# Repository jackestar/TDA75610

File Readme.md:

# TDA75610 Development Board (Placa de desarrollo)

[Blog](https://jackestar.netlify.app/Blog/Kicad/TDA75610.html)
[Esquematico](https://drive.google.com/file/d/1zOZ_QLpb7rlT-NX607TR__lV9A5XwjoH/view?usp=sharing)

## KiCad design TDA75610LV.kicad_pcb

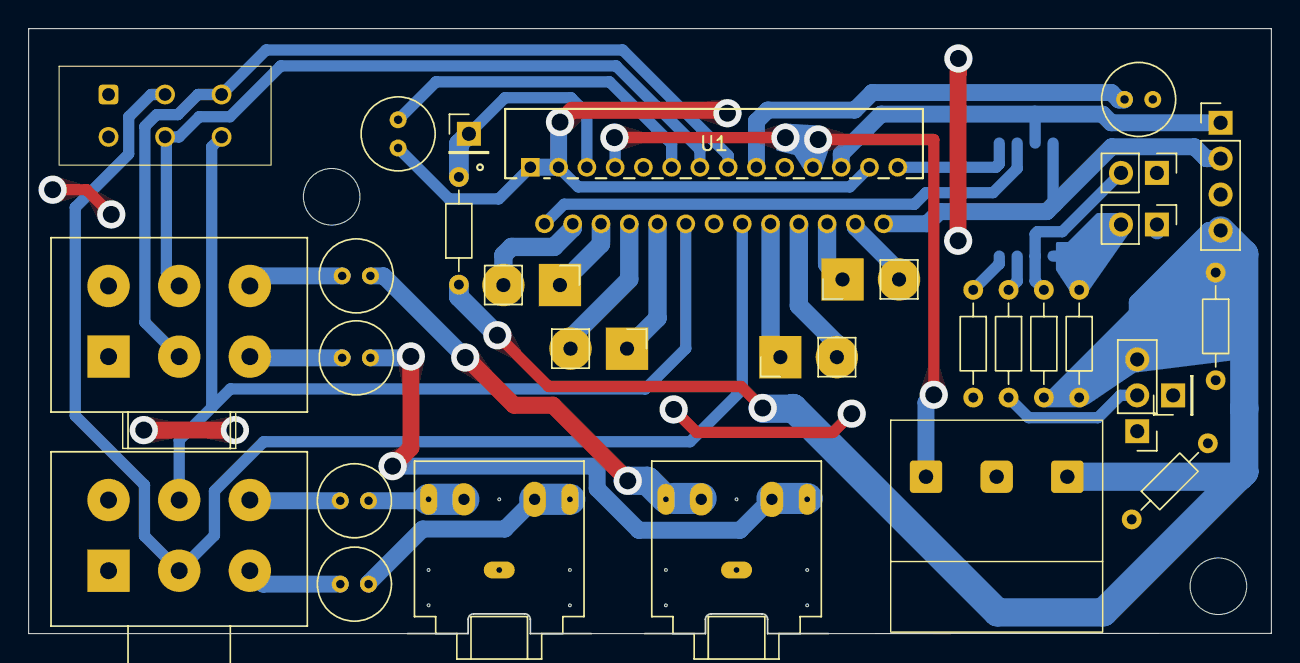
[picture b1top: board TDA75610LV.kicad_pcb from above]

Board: 2 copper layers, 87.9 x 42.8 mm, 31 parts (1 on the bottom side), 36 nets.

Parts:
C3: 10u; C_Radial_D5.0mm_H7.0mm_P2.00mm
C4, C5, C6, C7, C8: .22u; C_Radial_D5.0mm_H7.0mm_P2.00mm
J2, J3, J4, J5: Output1; PinHeader_1x02_P4mm_Vertical
J6: FB; Jack_3.5mm_CUI_SJ1-3525N_Horizontal
J7: RL; Jack_3.5mm_CUI_SJ1-3525N_Horizontal
J8: I2C; PinHeader_1x04_P2.54mm_Vertical
J9: ADSEL-HE; PinHeader_1x02_P2.54mm_Vertical
J10: ADSEL-Gain; PinHeader_1x02_P2.54mm_Vertical
J11: ADSEL-STBY; PinHeader_1x03_P2.54mm_Vertical
J12: ADSEL-STBY-Mute; PinHeader_1x01_P2.54mm_Vertical
J13: Clip Detector Out; PinHeader_1x01_P2.54mm_Vertical
J15: Out; BlockTerminal_1x03_15mmx15mm_P5mm_Vertical
R4: 10k; R_Axial_DIN0204_L3.6mm_D1.6mm_P7.62mm_Horizontal
R5, R8, R9: 1k; R_Axial_DIN0204_L3.6mm_D1.6mm_P7.62mm_Horizontal
R6: 560; R_Axial_DIN0204_L3.6mm_D1.6mm_P7.62mm_Horizontal
R7: 330; R_Axial_DIN0204_L3.6mm_D1.6mm_P7.62mm_Horizontal
R10: 47k; R_Axial_DIN0204_L3.6mm_D1.6mm_P7.62mm_Horizontal
RV1, RV2: 50k; Potentiometer_Alps_RK163_Dual_Horizontal
SW1: 2C/4C; SW_CK_JS202011CQN_DPDT_Straight
SW2: Mode; A6H-4101
U1: TDA75610LV; FLEXIWATT27_VERTICAL_STM

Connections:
+5V: J8.4, J11.3, J15.3, R6.1, R8.2, R9.2, R10.1
/3.2v: J12.1, R5.2, R6.2
CD: J13.1, R10.2, U1.5 (CD-OUT)
CLK: J8.1, SW2.7, U1.23 (CK)
DTA: J8.2, SW2.8, U1.26 (DATA)
GND: C3.2, C8.2, J6.S, J7.S, J8.3, J9.1, J10.1, J11.1, J15.2, R5.1, R7.2, RV1.1, RV1.4, RV2.1, RV2.4, U1.1 (TAB), U1.3 (PWGND2), U1.9 (PWGND1), U1.14 (SGND), U1.19 (PWGND3), U1.25 (PWGND4)
In1: RV2.5, SW1.4 (A), U1.12 (IN1)
In2: RV1.5, SW1.5 (B), U1.13 (IN2)
In3: RV2.2, SW1.2 (B), U1.16 (IN3)
In4: RV1.2, SW1.3 (C), U1.15 (IN4)
unnamed: C4.1, RV1.6
unnamed: C4.2, J7.R, J7.RN
unnamed: C5.1, RV1.3
unnamed: C5.2, J7.T, J7.TN
unnamed: C6.1, RV2.3
unnamed: C6.2, J6.T, J6.TN
unnamed: C7.1, RV2.6
unnamed: C7.2, J6.R, J6.RN
unnamed: J9.2, R9.1, SW2.2
unnamed: J10.2, R8.1, SW2.1
unnamed: J11.2, R4.2
unnamed: R4.1, SW2.3
unnamed: R7.1, SW2.4
unnamed: C8.1, U1.17 (ACGND)
unnamed: C3.1, U1.11 (SVR)
Out1+: J2.1, U1.10 (OUT1+)
Out1-: J2.2, U1.8 (OUT1-)
Out2+: J3.1, U1.6 (OUT2+)
Out2-: J3.2, U1.4 (OUT2-)
Out3+: J4.1, U1.18 (OUT3+)
Out3-: J4.2, U1.20 (OUT3-)
Out4+: J5.1, U1.22 (OUT4+)
Out4-: J5.2, U1.24 (OUT4-)
SEL/I2C: SW2.5, U1.27 (ADSEL/I2CDIS)
STBY: SW2.6, U1.2 (STBY)
VCC: J15.1, U1.7 (VCC1), U1.21 (VCC2)

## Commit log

2025-07-22 First Tested Board
2025-07-22 Update Readme.md broke URL
